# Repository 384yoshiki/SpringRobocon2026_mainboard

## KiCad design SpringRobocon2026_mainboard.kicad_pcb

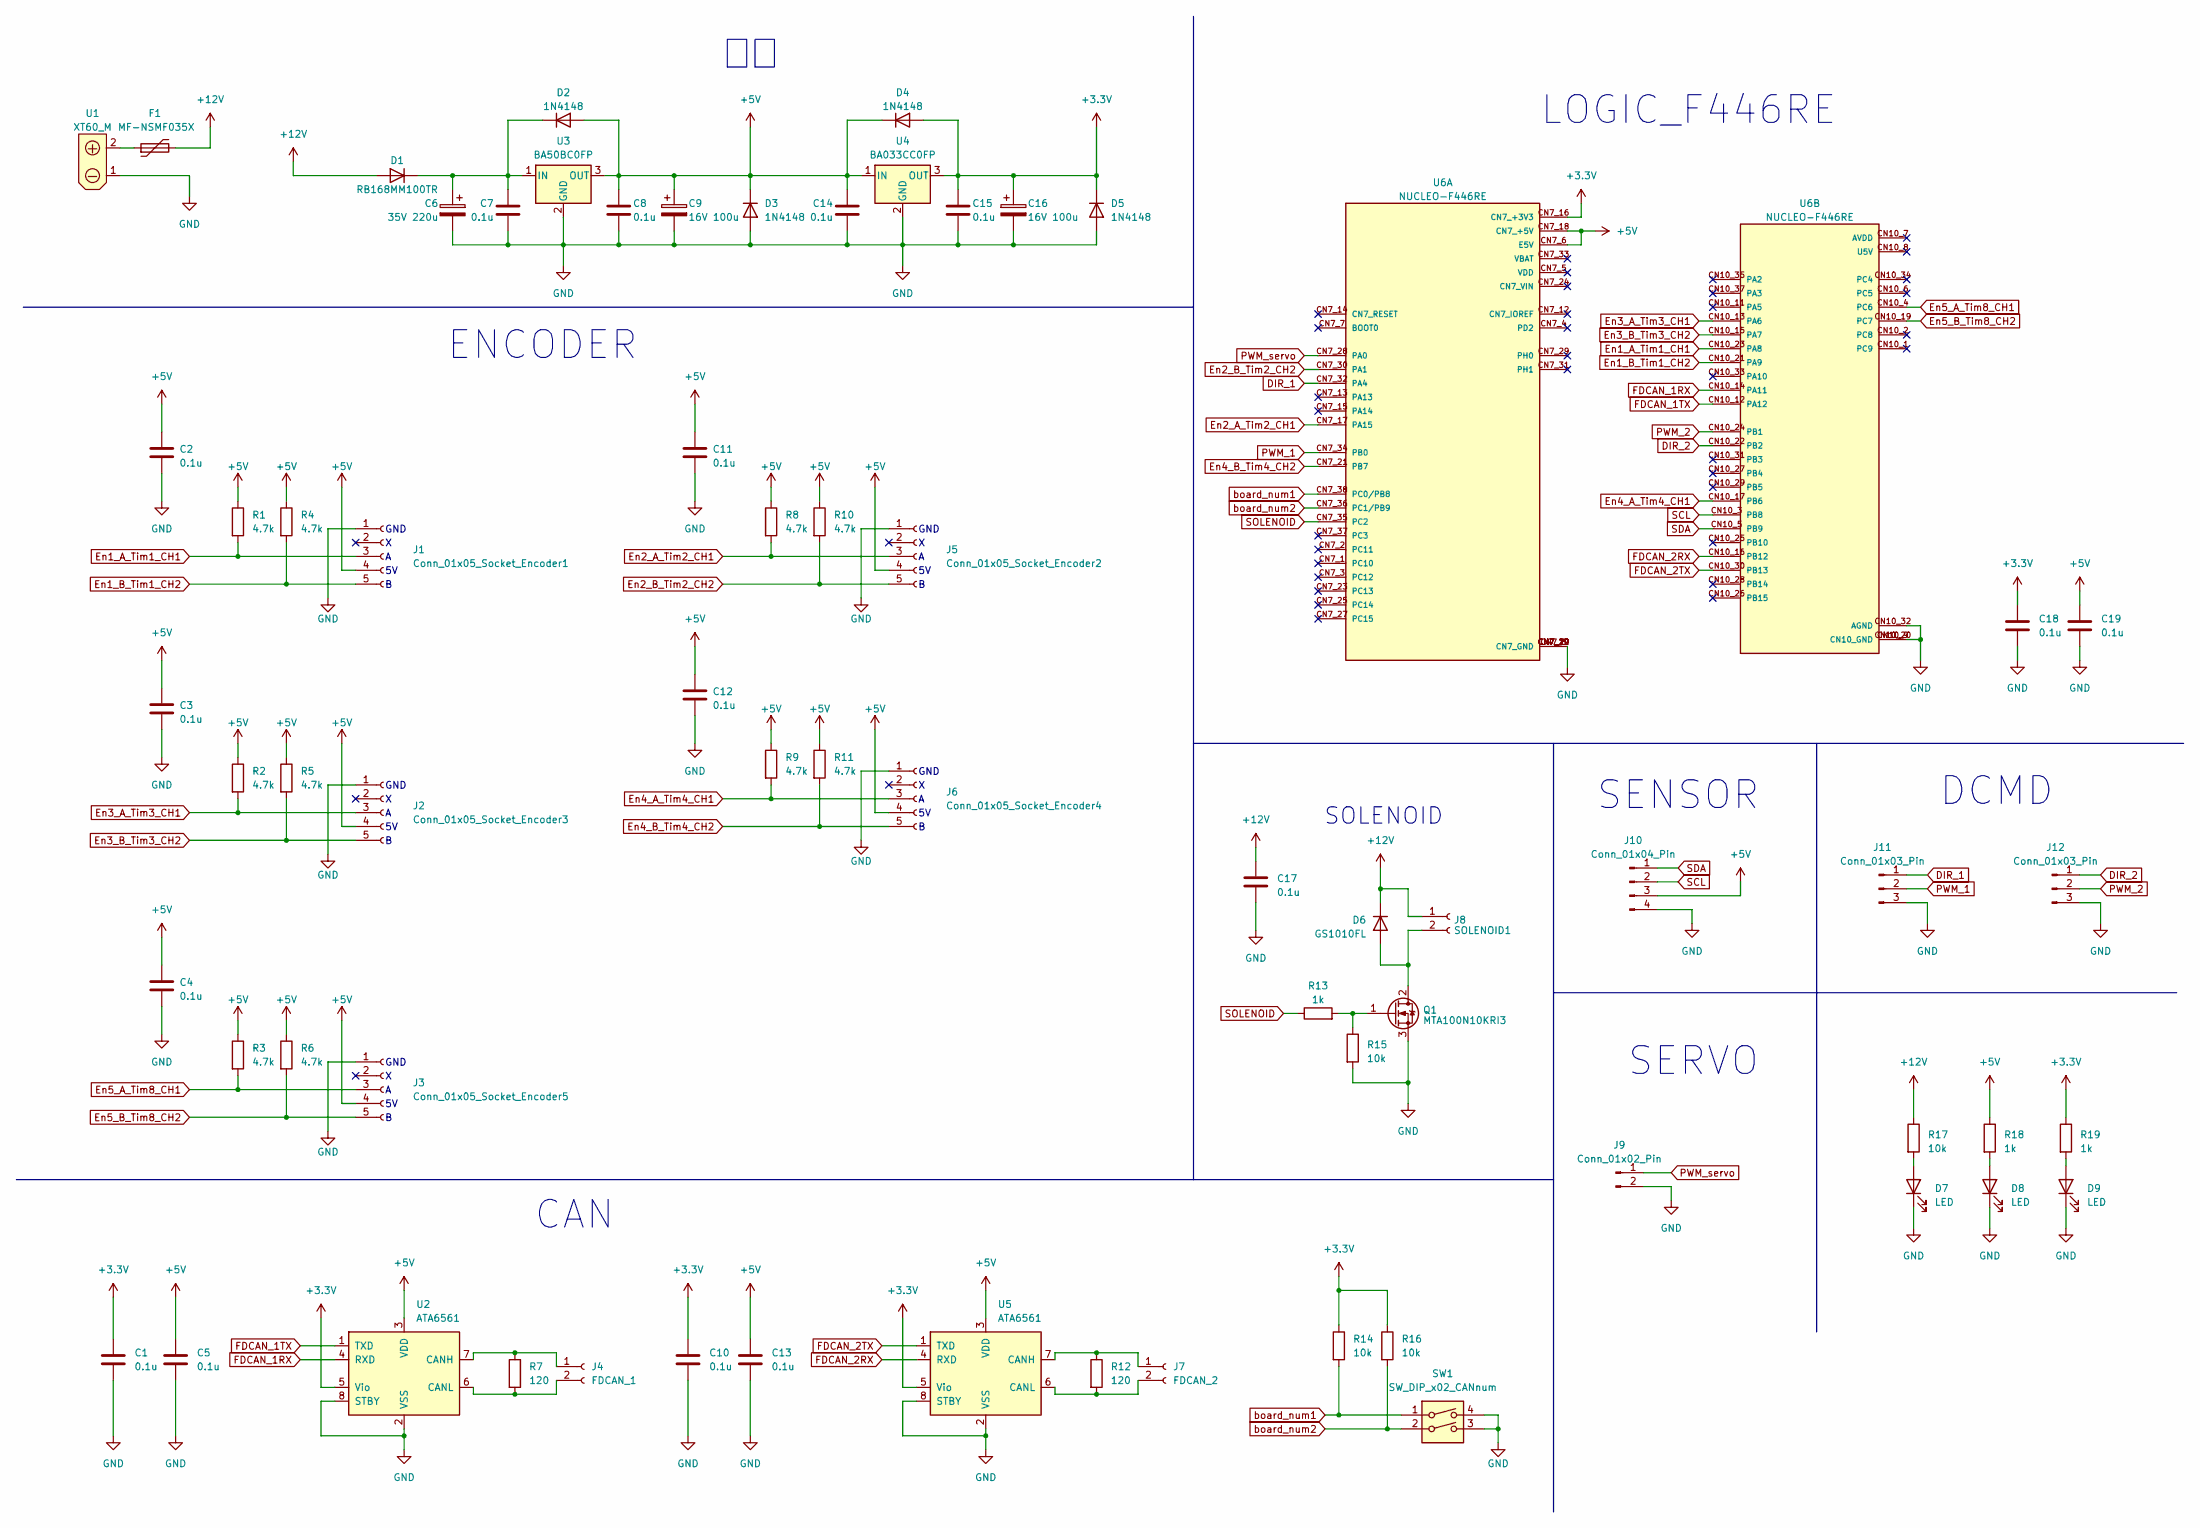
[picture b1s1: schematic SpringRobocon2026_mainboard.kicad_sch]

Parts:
C1, C2, C3, C4, C5, C7, C8, C10, C11, C12, C13, C14, C15, C17, C18, C19: 0.1u; C_0603_1608Metric_Pad1.08x0.95mm_HandSolder
C6: 35V 220u; CP_Radial_D8.0mm_P3.50mm
C9, C16: 16V 100u; CP_Radial_D5.0mm_P2.00mm
D1: RB168MM100TR; D_SOD-123_HandSolder
D2, D3, D4, D5: 1N4148; D_SOD-123_HandSolder
D6: GS1010FL; D_SOD-123F
D7, D8, D9: LED; LED_D3.0mm
F1: MF-NSMF035X; PolyFuse_MF-NSMF-series
J1: Conn_01x05_Socket_Encoder1; Pocket_Header_ver
J2: Conn_01x05_Socket_Encoder3; Pocket_Header_ver
J3: Conn_01x05_Socket_Encoder5; Pocket_Header_ver
J4: FDCAN_1; JST_XH_B2B-XH-A_1x02_P2.50mm_Vertical
J5: Conn_01x05_Socket_Encoder2; Pocket_Header_ver
J6: Conn_01x05_Socket_Encoder4; Pocket_Header_ver
J7: FDCAN_2; JST_XH_B2B-XH-A_1x02_P2.50mm_Vertical
J8: SOLENOID1; JST_XH_B2B-XH-A_1x02_P2.50mm_Vertical
J9: Conn_01x02_Pin; PinHeader_1x02_P2.54mm_Vertical
J10: Conn_01x04_Pin; PinHeader_1x04_P2.54mm_Vertical
J11, J12: Conn_01x03_Pin; JST_XH_B3B-XH-A_1x03_P2.50mm_Vertical
Q1: MTA100N10KRI3; TO-251-3_Vertical
R1, R2, R3, R4, R5, R6, R8, R9, R10, R11: 4.7k; R_0603_1608Metric_Pad0.98x0.95mm_HandSolder
R7, R12: 120; R_0603_1608Metric_Pad0.98x0.95mm_HandSolder
R13, R18, R19: 1k; R_0603_1608Metric_Pad0.98x0.95mm_HandSolder
R14, R15, R16, R17: 10k; R_0603_1608Metric_Pad0.98x0.95mm_HandSolder
SW1: SW_DIP_x02_CANnum; SW_DIP_SPSTx02_Slide_6.7x6.64mm_W7.62mm_P2.54mm_LowProfile
U1: XT60_M; AMASS_XT60-M_1x02_P7.20mm_Vertical
U2, U5: ATA6561
U3: BA50BC0FP; TO-252-2
U4: BA033CC0FP; TO-252-2
U6: NUCLEO-F446RE; PARTREV 13

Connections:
+3.3V: C1.1, C10.1, C15.1, C16.1, C18.1, D4.2 (A), D5.1 (K), R14.1, R16.1, R19.1, U2.5 (Vio), U4.3 (OUT), U5.5 (Vio), U6.CN7_16 (CN7_+3V3)
+5V: C2.1, C3.1, C4.1, C5.1, C8.1, C9.1, C11.1, C12.1, C13.1, C14.1, C19.1, D2.2 (A), D3.1 (K), D4.1 (K), J1.4, J2.4, J3.4, J5.4, J6.4, J10.3, R1.1, R2.1, R3.1, R4.1, R5.1, R6.1, R8.1, R9.1, R10.1, R11.1, R18.1, U2.3 (VDD), U3.3 (OUT), U4.1 (IN), U5.3 (VDD), U6.CN7_6 (E5V), U6.CN7_18 (CN7_+5V); also elsewhere on the board
+12V: C17.1, D1.2 (A), D6.1 (K), F1.2, J8.1, R17.1
DIR_1: J11.1, U6.CN7_32 (PA4)
DIR_2: J12.1, U6.CN10_22 (PB2)
En1_A_Tim1_CH1: J1.3, R1.2, U6.CN10_23 (PA8)
En1_B_Tim1_CH2: J1.5, R4.2, U6.CN10_21 (PA9)
En2_A_Tim2_CH1: J5.3, R8.2, U6.CN7_17 (PA15)
En2_B_Tim2_CH2: J5.5, R10.2, U6.CN7_30 (PA1)
En3_A_Tim3_CH1: J2.3, R2.2, U6.CN10_13 (PA6)
En3_B_Tim3_CH2: J2.5, R5.2, U6.CN10_15 (PA7)
En4_A_Tim4_CH1: J6.3, R9.2, U6.CN10_17 (PB6)
En4_B_Tim4_CH2: J6.5, R11.2, U6.CN7_21 (PB7)
En5_A_Tim8_CH1: J3.3, R3.2, U6.CN10_4 (PC6)
En5_B_Tim8_CH2: J3.5, R6.2, U6.CN10_19 (PC7)
FDCAN_1RX: U2.4 (RXD), U6.CN10_14 (PA11)
FDCAN_1TX: U2.1 (TXD), U6.CN10_12 (PA12)
FDCAN_2RX: U5.4 (RXD), U6.CN10_16 (PB12)
FDCAN_2TX: U5.1 (TXD), U6.CN10_30 (PB13)
GND: C1.2, C2.2, C3.2, C4.2, C5.2, C6.2, C7.2, C8.2, C9.2, C10.2, C11.2, C12.2, C13.2, C14.2, C15.2, C16.2, C17.2, C18.2, C19.2, D3.2 (A), D5.2 (A), D7.1 (K), D8.1 (K), D9.1 (K), J1.1, J2.1, J3.1, J5.1, J6.1, J9.2, J10.4, J11.3, J12.3, Q1.3 (S), R15.2, SW1.3, SW1.4, U1.1, U2.2 (VSS), U2.8 (STBY), U3.2 (GND), U4.2 (GND), U5.2 (VSS), U5.8 (STBY), U6.CN7_8 (CN7_GND), U6.CN7_19 (CN7_GND), U6.CN7_20 (CN7_GND), U6.CN7_22 (CN7_GND), U6.CN10_9 (CN10_GND), U6.CN10_20 (CN10_GND), U6.CN10_32 (AGND); also elsewhere on the board
unnamed: C6.1, C7.1, D1.1 (K), D2.1 (K), U3.1 (IN)
unnamed: D6.2 (A), J8.2, Q1.2 (D)
unnamed: D7.2 (A), R17.2
unnamed: D8.2 (A), R18.2
unnamed: D9.2 (A), R19.2
unnamed: F1.1, U1.2
unnamed: J4.1, R7.1, U2.7 (CANH)
unnamed: J4.2, R7.2, U2.6 (CANL)
unnamed: J7.1, R12.1, U5.7 (CANH)
unnamed: J7.2, R12.2, U5.6 (CANL)
unnamed: Q1.1 (G), R13.2, R15.1
PWM_1: J11.2, U6.CN7_34 (PB0)
PWM_2: J12.2, U6.CN10_24 (PB1)
PWM_servo: J9.1, U6.CN7_28 (PA0)
SCL: J10.2, U6.CN10_3 (PB8)
SDA: J10.1, U6.CN10_5 (PB9)
SOLENOID: R13.1, U6.CN7_35 (PC2)
board_num1: R14.2, SW1.1, U6.CN7_38 (PC0/PB8)
board_num2: R16.2, SW1.2, U6.CN7_36 (PC1/PB9)

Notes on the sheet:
SENSOR
SOLENOID
GND
ENCODER
LOGIC_F446RE
CAN
DCMD
SERVO

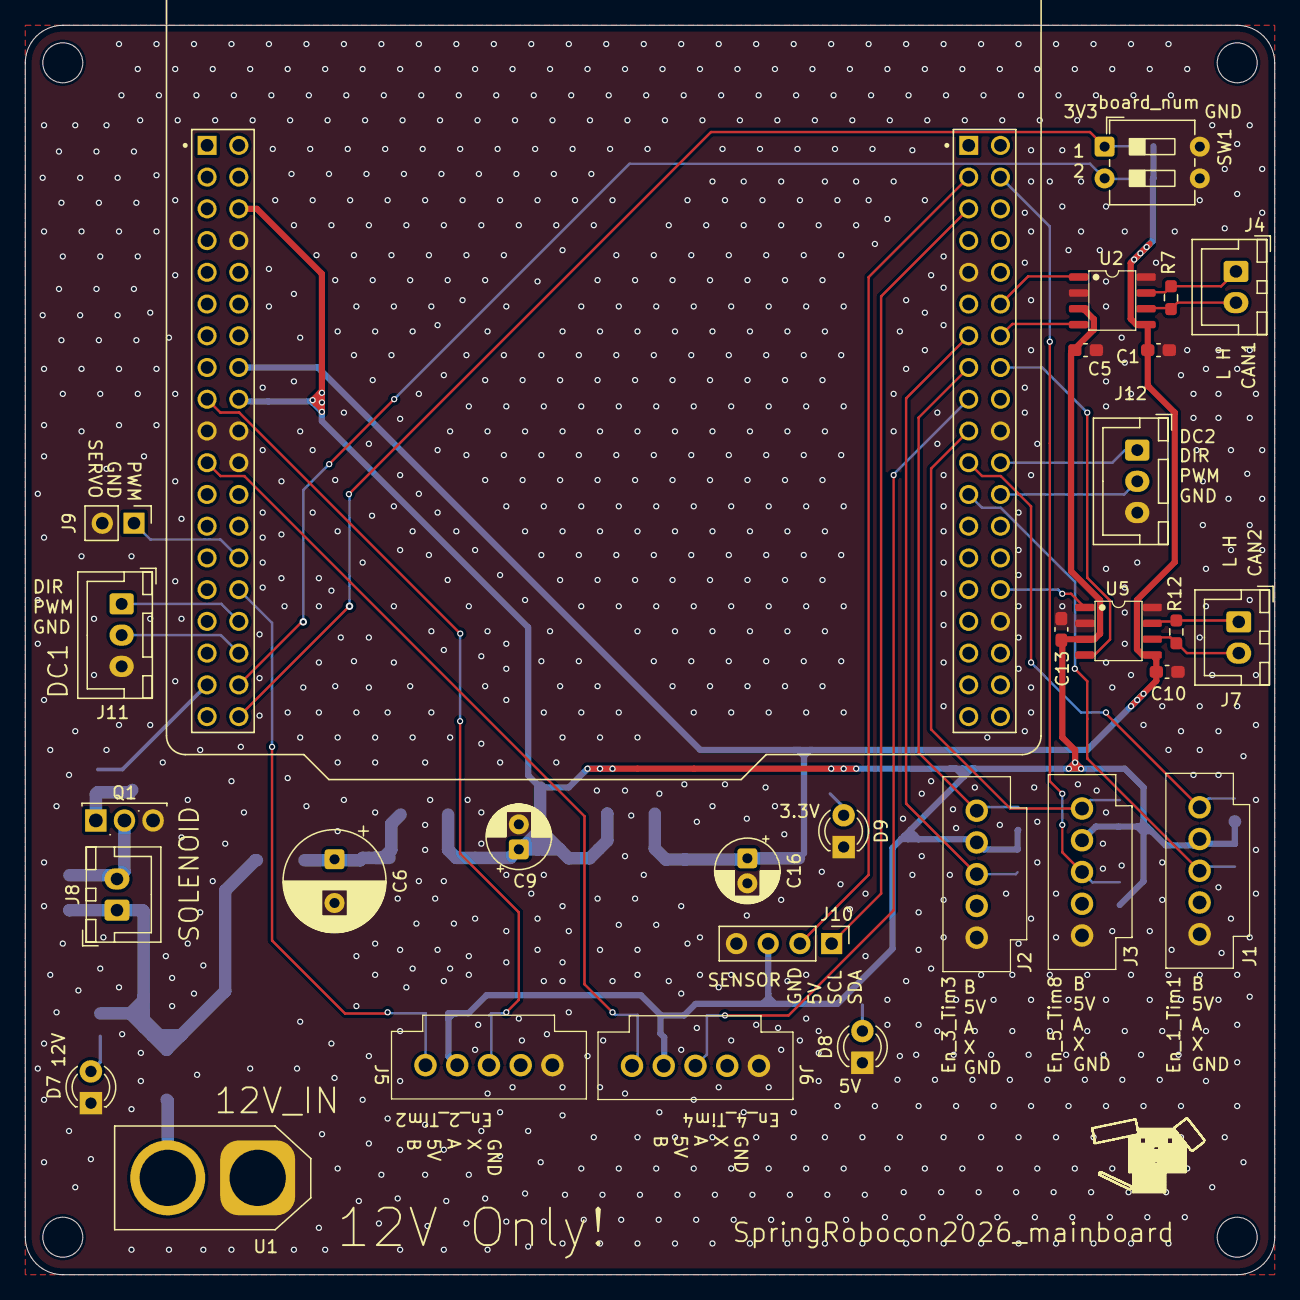
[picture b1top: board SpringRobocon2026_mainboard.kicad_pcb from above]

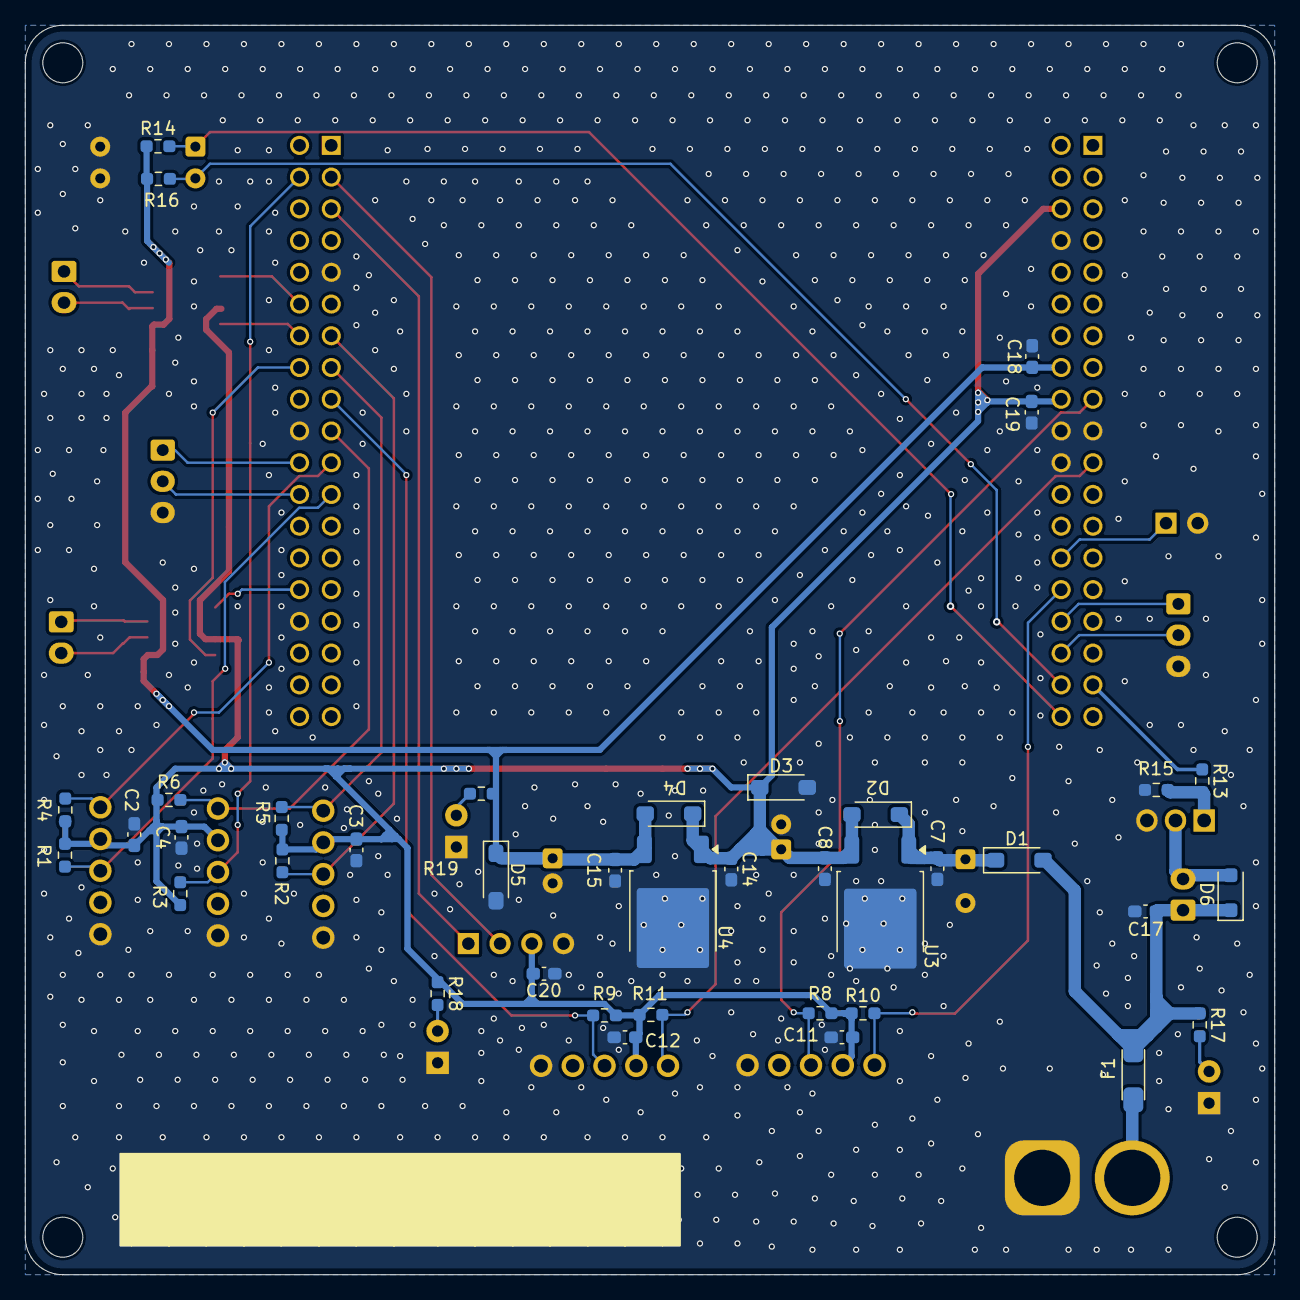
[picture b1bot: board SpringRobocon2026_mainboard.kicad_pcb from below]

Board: 2 copper layers, 100.0 x 100.0 mm, 70 parts (39 on the bottom side), 39 nets.

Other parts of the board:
C20: 0.1u; C_0603_1608Metric_Pad1.08x0.95mm_HandSolder
ref**: val**; ROGIKEN

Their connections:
+5V: C20.1; also elsewhere on the board
GND: C20.2; also elsewhere on the board

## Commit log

2025-12-17 回路図ちょっと変更、フットプリント割り当て
2025-12-19 回路図更新
2025-12-22 PCB編集
2025-12-24 配線始まり
2025-12-27 配線更新
2025-12-27 一旦完成
2025-12-29 3回目修正
2025-12-29 6回目修正
